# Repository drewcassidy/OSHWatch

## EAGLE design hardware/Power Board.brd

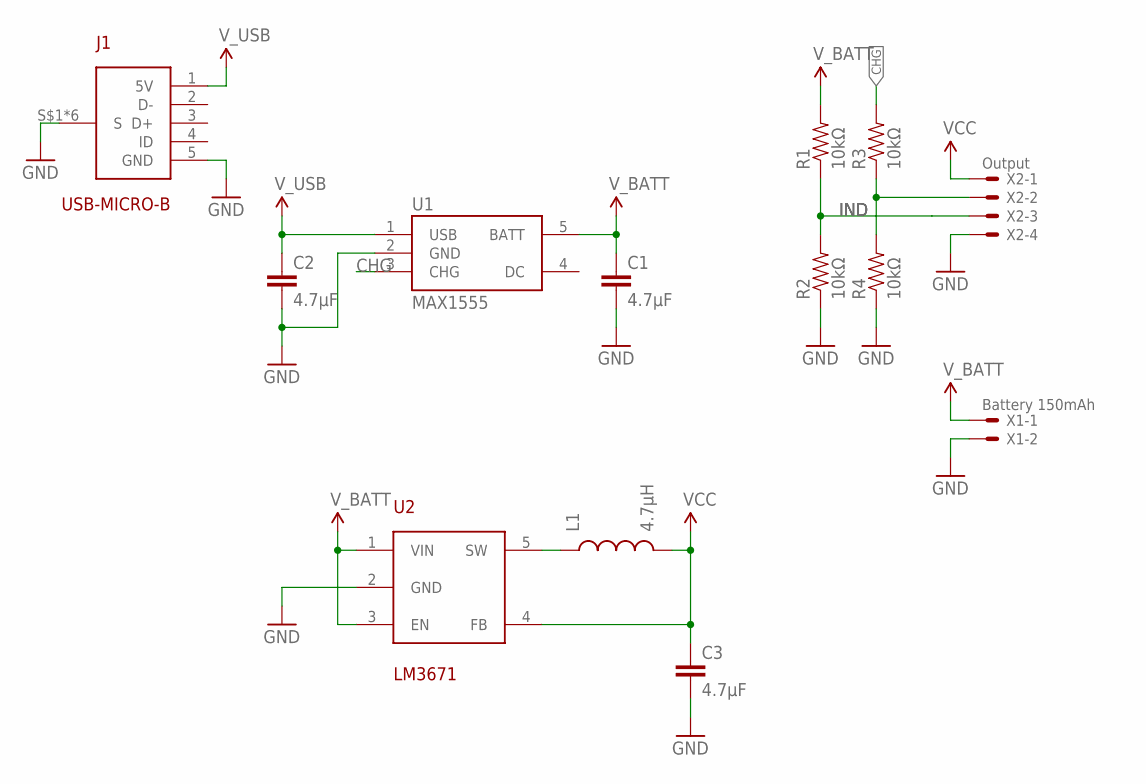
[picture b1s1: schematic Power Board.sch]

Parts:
C1, C2, C3: 4.7µF; 0805
J1: USB-MICRO-B; UB-MC5BR3
L1: 4.7µH; 0805
R1, R2, R3, R4: 10kΩ; 0805
U1: MAX1555; SOT23-5
U2: LM3671; SOT23-5
X1: Battery 150mAh; SM02B-SRSS-TB
X2: Output; SM04B-SRSS-TB

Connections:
CHG: R3.2, U1.3 (CHG)
CHG_2: R3.1, R4.2, X2.2
GND: C1.2, C2.2, C3.2, J1.5 (GND), J1.S$1 (S), J1.S$2 (S), J1.S$3 (S), J1.S$4 (S), J1.S$5 (S), J1.S$6 (S), R2.1, R4.1, U1.2 (GND), U2.2 (GND), X1.2, X2.4
IND: R1.1, R2.2, X2.3
unnamed: L1.1, U2.5 (SW)
VCC: C3.1, L1.2, U2.4 (FB), X2.1
V_BATT: C1.1, R1.2, U1.5 (BATT), U2.1 (VIN), U2.3 (EN), X1.1
V_USB: C2.1, J1.1 (5V), U1.1 (USB)

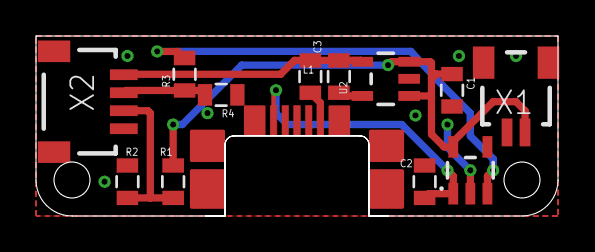
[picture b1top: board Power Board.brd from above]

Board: 2 copper layers, 29.0 x 10.0 mm, 13 parts (0 on the bottom side), 8 nets.

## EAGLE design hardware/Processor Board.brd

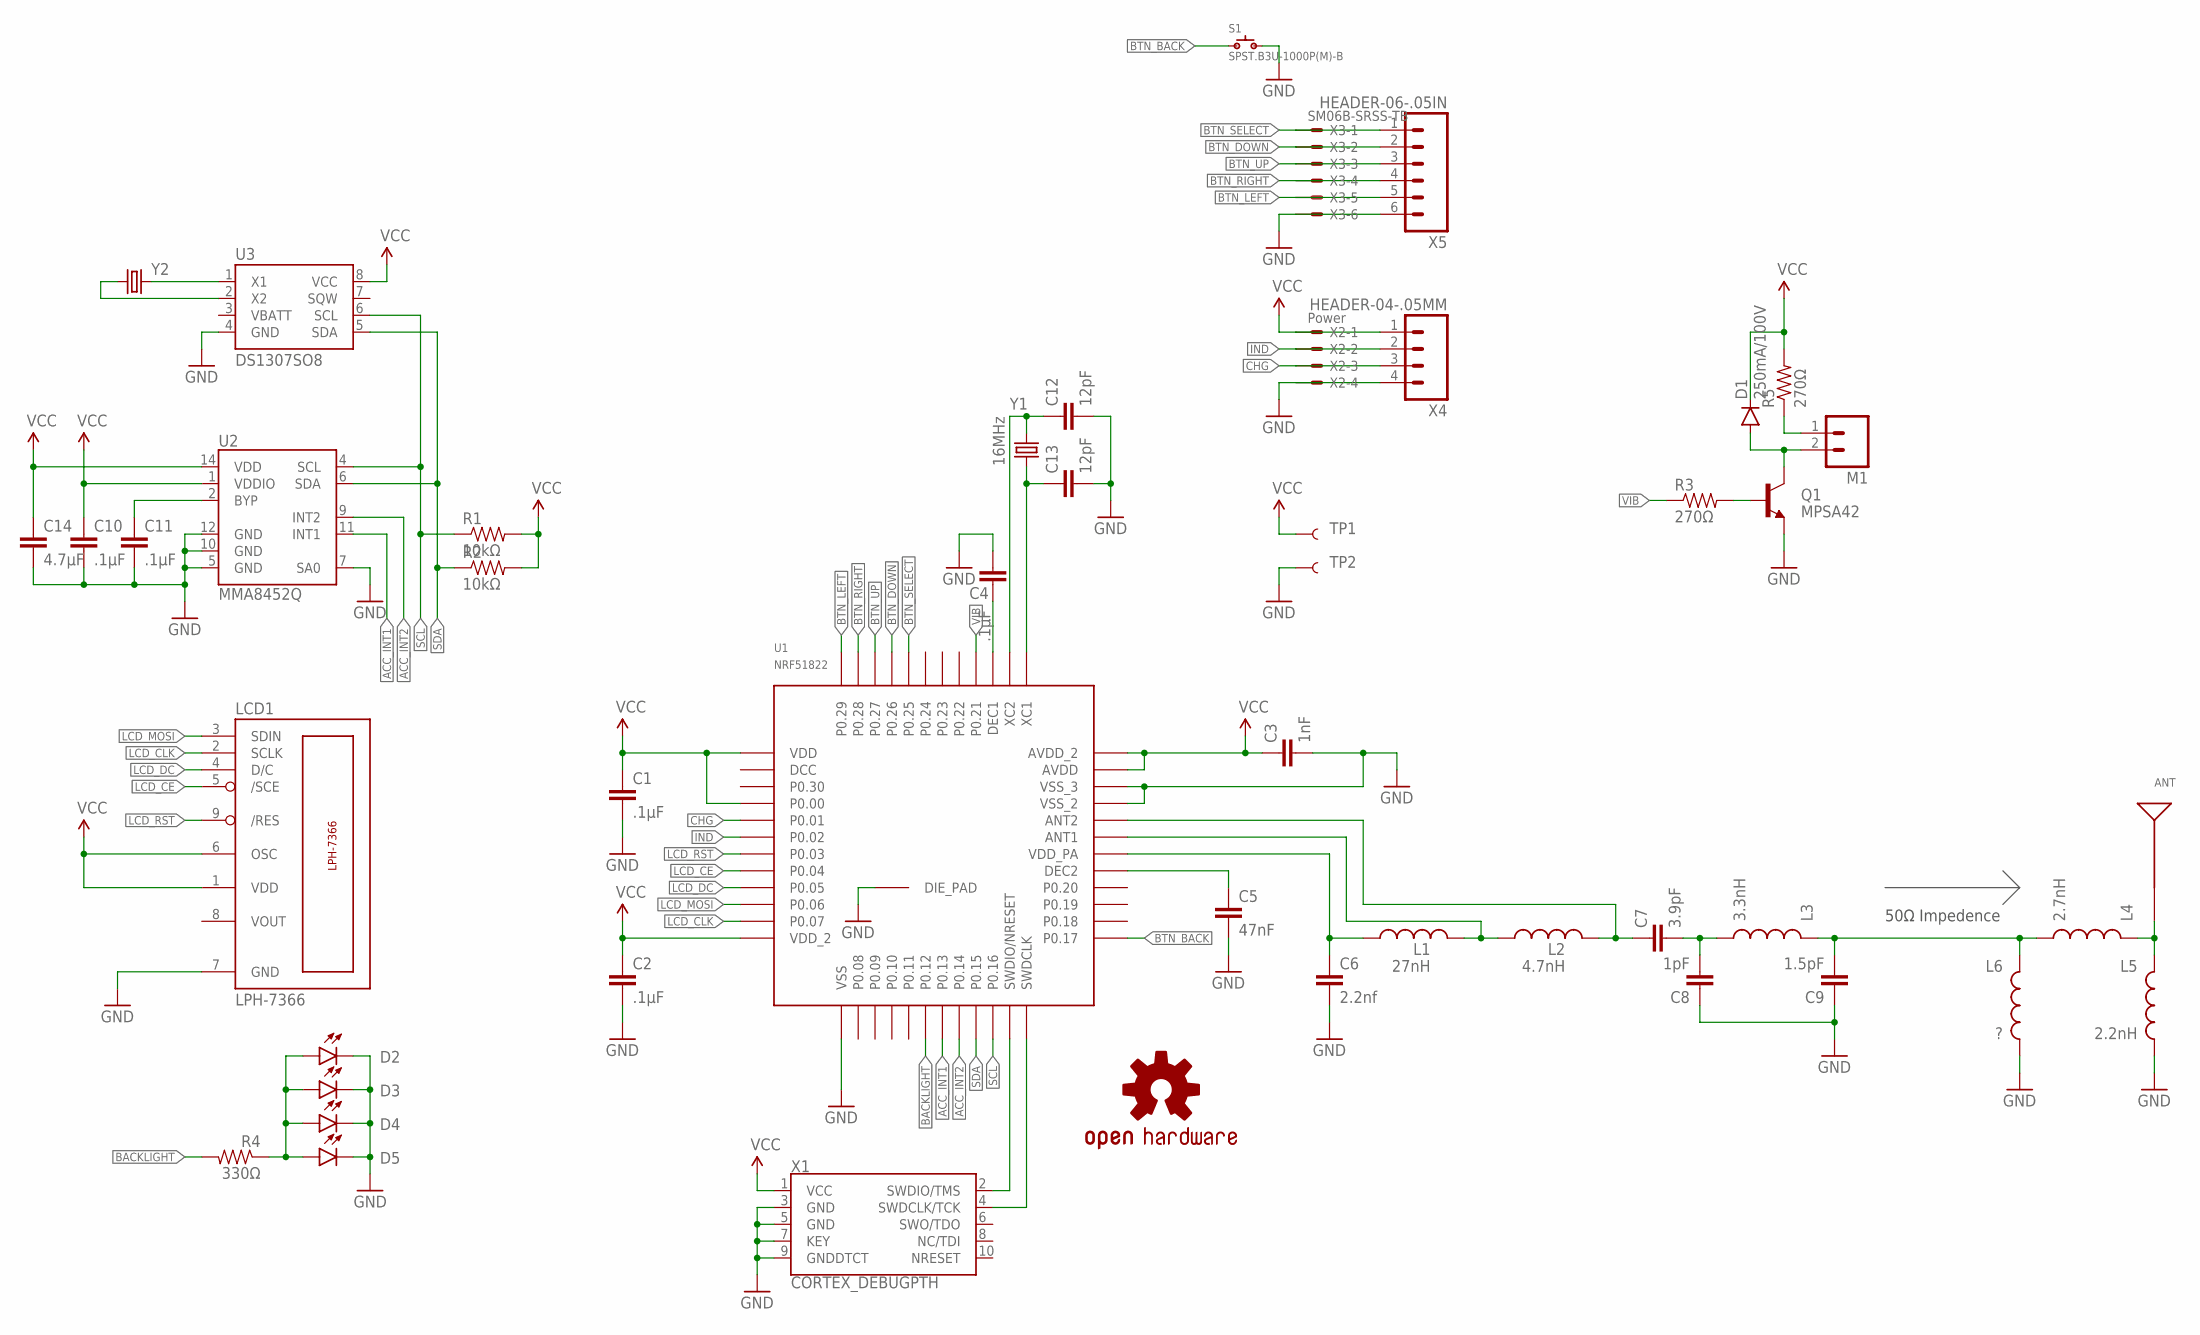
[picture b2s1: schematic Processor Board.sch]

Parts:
ANT: ANTENNA_CHIP2450AT43B100; AT43B
C1, C2, C4, C10, C11: .1µF; 0805
C3: 1nF; 0805
C5: 47nF; 0805
C6: 2.2nf; 0805
C7: 3.9pF; 0805
C8: 1pF; 0805
C9: 1.5pF; 0805
C12, C13: 12pF; 0805
C14: 4.7µF; 0805
D1: 250mA/100V; SOD-323
D2, D3, D4, D5: LED1206; LED-1206
L1: 27nH; 0805
L2: 4.7nH; 0805
L3: 3.3nH; 0805
L4: 2.7nH; 0805
L5: 2.2nH; 0805
L6: ?; 0805
LCD1: LPH-7366
LOGO1: OSHW-LOGOL-COPPER; OSHW-LOGO-L_COPPER
M1: M021X02_NO_SILK; 1X02_NO_SILK
Q1: MPSA42; SOT23-3
R1, R2: 10kΩ; 0805
R3, R5: 270Ω; 0805
R4: 330Ω; 0805
S1: SPST.B3U-1000P(M)-B; B3U-1000P(M)-B
TP1, TP2: TEST-POINT3; PAD.03X.03
U1: NRF51822; QFN48
U2: MMA8452Q; QFN-16_0.5MM
U3: DS1307SO8; SO08
X1: CORTEX_DEBUGPTH; 2X5-PTH-1.27MM
X2: Power; SM04B-SRSS-TB
X3: SM06B-SRSS-TB
X4: HEADER-04-.05MM; HEADER-04-.05IN
X5: HEADER-06-.05IN
Y1: 16MHz; CRYSTAL-SMD-5X3
Y2: CRYSTAL32-SMD-MELF; CRYSTAL-32KHZ-SMD-MELF

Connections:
ACC_INT1: U1.19 (P0.13), U2.11 (INT1)
ACC_INT2: U1.20 (P0.14), U2.9 (INT2)
ANT: ANT.ANT, L4.1, L5.1
ANT1: L1.1, L2.2, U1.31 (ANT1)
ANT2: C7.1, L2.1, U1.32 (ANT2)
BACKLIGHT: R4.2, U1.18 (P0.12)
BTN_BACK: S1.1, U1.25 (P0.17)
BTN_DOWN: U1.45 (P0.26), X3.2, X5.2
BTN_LEFT: U1.48 (P0.29), X3.5, X5.5
BTN_RIGHT: U1.47 (P0.28), X3.4, X5.4
BTN_SELECT: U1.44 (P0.25), X3.1, X5.1
BTN_UP: U1.46 (P0.27), X3.3, X5.3
CHG: U1.5 (P0.01), X2.3, X4.3
F_1: C7.2, C8.2, L3.2
F_2: C9.2, L3.1, L4.2, L6.1
GND: C1.2, C2.2, C3.2, C4.1, C5.2, C6.2, C8.1, C9.1, C10.2, C11.2, C12.1, C13.1, C14.2, D2.C, D3.C, D4.C, D5.C, L5.2, L6.2, LCD1.7 (GND), Q1.2 (E), S1.2, TP2.P$1, U1.13 (VSS), U1.33 (VSS_2), U1.34 (VSS_3), U1.GND (DIE_PAD), U2.5 (GND), U2.7 (SA0), U2.10 (GND), U2.12 (GND), U3.4 (GND), X1.3 (GND), X1.5 (GND), X1.7 (KEY), X1.9 (GNDDTCT), X2.4, X3.6, X4.4, X5.6
IND: U1.6 (P0.02), X2.2, X4.2
LCD_CE: LCD1.5 (/SCE), U1.8 (P0.04)
LCD_CLK: LCD1.2 (SCLK), U1.11 (P0.07)
LCD_DC: LCD1.4 (D/C), U1.9 (P0.05)
LCD_MOSI: LCD1.3 (SDIN), U1.10 (P0.06)
LCD_RST: LCD1.9 (/RES), U1.7 (P0.03)
unnamed: U1.24 (SWDCLK), X1.4 (SWDCLK/TCK)
unnamed: C4.2, U1.39 (DEC1)
unnamed: U1.23 (SWDIO/NRESET), X1.2 (SWDIO/TMS)
unnamed: C5.1, U1.29 (DEC2)
unnamed: C11.1, U2.2 (BYP)
unnamed: Q1.1 (B), R3.2
unnamed: C12.2, U1.38 (XC2), Y1.3 (2)
unnamed: C13.2, U1.37 (XC1), Y1.1
unnamed: U3.1 (X1), Y2.X2 (2)
unnamed: D1.A, M1.2, Q1.3 (C)
unnamed: M1.1, R5.1
unnamed: U3.2 (X2), Y2.X1 (1)
unnamed: D2.A, D3.A, D4.A, D5.A, R4.1
SCL: R1.1, U1.22 (P0.16), U2.4 (SCL), U3.6 (SCL)
SDA: R2.1, U1.21 (P0.15), U2.6 (SDA), U3.5 (SDA)
VCC: C1.1, C2.1, C3.1, C10.1, C14.1, D1.C, LCD1.1 (VDD), LCD1.6 (OSC), R1.2, R2.2, R5.2, TP1.P$1, U1.1 (VDD), U1.4 (P0.00), U1.12 (VDD_2), U1.35 (AVDD), U1.36 (AVDD_2), U2.1 (VDDIO), U2.14 (VDD), U3.8 (VCC), X1.1 (VCC), X2.1, X4.1
VDD_PA: C6.1, L1.2, U1.30 (VDD_PA)
VIB: R3.1, U1.40 (P0.21)

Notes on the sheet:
50Ω Impedence

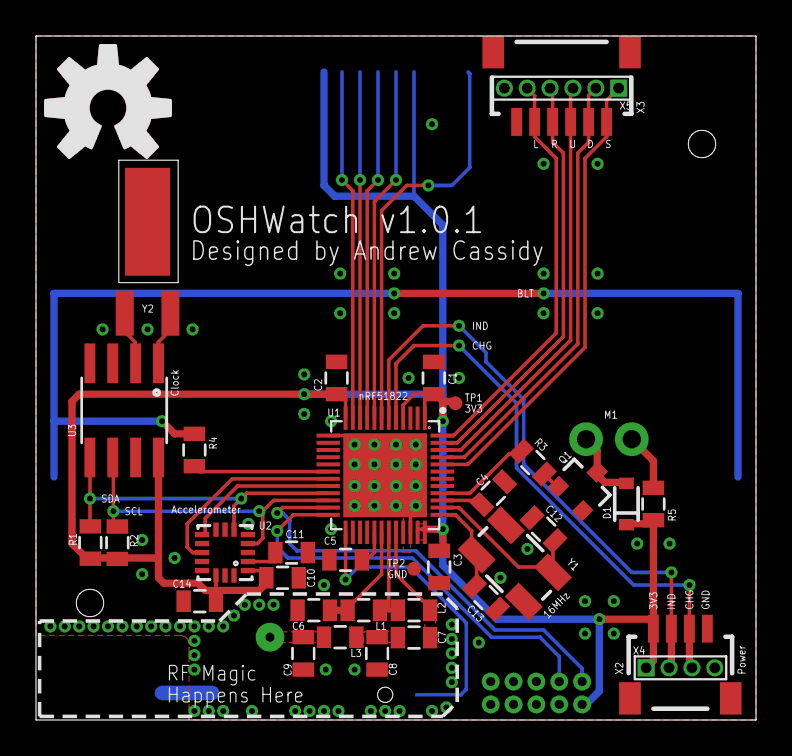
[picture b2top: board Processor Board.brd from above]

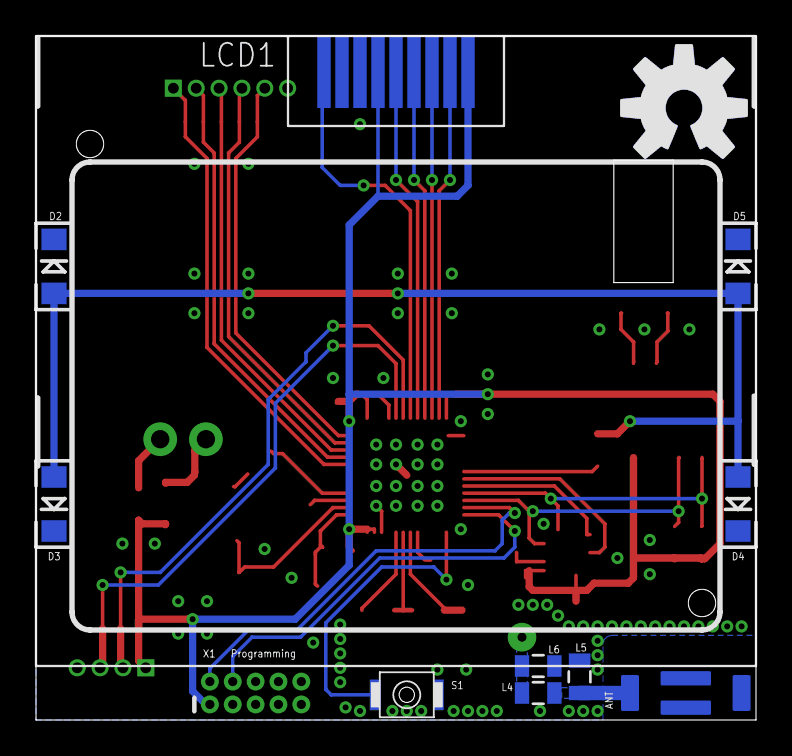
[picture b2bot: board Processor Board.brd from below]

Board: 2 copper layers, 40.0 x 38.0 mm, 51 parts (13 on the bottom side), 40 nets.

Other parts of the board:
LOGO2: OSHW-LOGOL-COPPER; OSHW-LOGO-L_COPPER
U$1, U$2: OSHW-LOGO-L

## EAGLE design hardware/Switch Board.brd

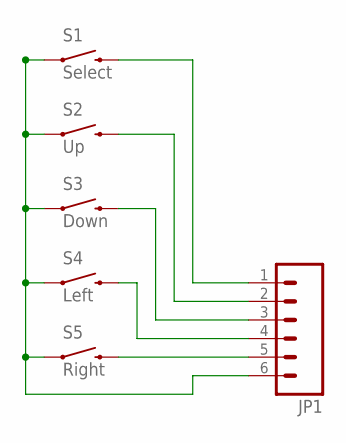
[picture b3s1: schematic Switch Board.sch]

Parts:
JP1: M06SMD-1MM; 1X06-1MM
S1: Select; TACTILE-SWITCH-SMD
S2: Up; TACTILE-SWITCH-SMD
S3: Down; TACTILE-SWITCH-SMD
S4: Left; TACTILE-SWITCH-SMD
S5: Right; TACTILE-SWITCH-SMD

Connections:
GND: JP1.6, S1.1, S2.1, S3.1, S4.1, S5.1
unnamed: JP1.5, S5.3 (2)
unnamed: JP1.4, S4.3 (2)
unnamed: JP1.3, S3.3 (2)
unnamed: JP1.2, S2.3 (2)
unnamed: JP1.1, S1.3 (2)

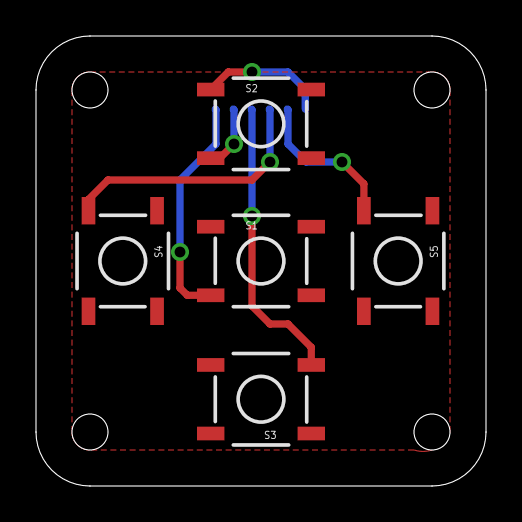
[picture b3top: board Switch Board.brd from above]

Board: 2 copper layers, 25.0 x 25.0 mm, 6 parts (1 on the bottom side), 6 nets.

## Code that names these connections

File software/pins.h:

#ifndef	PINS_H
#define	PINS_H

#define	CHG 		(p1)
#define IND			(p2)
#define LCD_RST		(p3)
#define LCD_CE		(p4)
#define LCD_DC		(p5)
#define LCD_MOSI 	(p6)
#define LCD_CLK		(p7)
#define BACKLIGHT   (p12)
#define ACC_INT1    (p13)
#define ACC_INT2    (p14)
#define SDA         (p15)
#define SDL         (p16)
#define BTN_BACK    (p17)
#define VIB         (p21)
#define BTN_SELECT  (p25)
#define BTN_DOWN    (p26)
#define BTN_UP      (p27)
#define BTN_RIGHT   (p28)
#define BTN_LEFT    (p29)

#endif

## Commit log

2016-03-14 Initialize with Yotta
2016-04-25 Add Power and Button boards
2016-09-18 Add bitmaps and python code to turn them into valid C++
    This python is an abomination 🙃🐍
2016-11-07 Ignore sublimetext projects
2016-11-07 BRANDING
2016-11-08 expand screen and watchface
2016-11-17 Rewrite bitmap generator to get the last byte
2016-12-16 migrate to mbedOS 5
    • delete yotta config files
    • move software to its own directory
    • reformat files
    • change includes to work with mbed OS 5
2016-12-16 move .clang-format
2016-12-17 Correct error in pins.h
2016-12-17 Fix for boards without the LFCLK
2016-12-17 Reorganize wathface.h's #includes
2016-12-17 expand pins.h to include buttons, I2C, and misc outputs
2016-12-17 adjust contrast to better match my test board
2016-12-23 Update Nokia library and test line drawing
2016-12-24 Optimize binary size
    now is smol
2016-12-24 Update Nokia Library again
2016-12-29 Migrate to Platformio
    • move source files to src/
    • add Travis.yml
    • add cmake files
2016-12-29 Migrate to Platformio (for real)
    • move source files to src/
    • add Travis.yml
    • add cmake files
2017-01-29 Add time management, RTC code, and watchface drawing
2017-01-29 Rename mainscreen.cpp to Mainscreen.cpp
2017-01-29 Rename mainscreen.h to Mainscreen.h
2017-02-01 Complete demo watchface • change '1' digit bitmap • finish watchface drawing program • add constants for day and month names

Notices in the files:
parts and their libraries:
SparkFun-Passives: Licensing: Creative Commons ShareAlike 4.0 International - https://creativecommons.org/licenses/by-sa/4.0
